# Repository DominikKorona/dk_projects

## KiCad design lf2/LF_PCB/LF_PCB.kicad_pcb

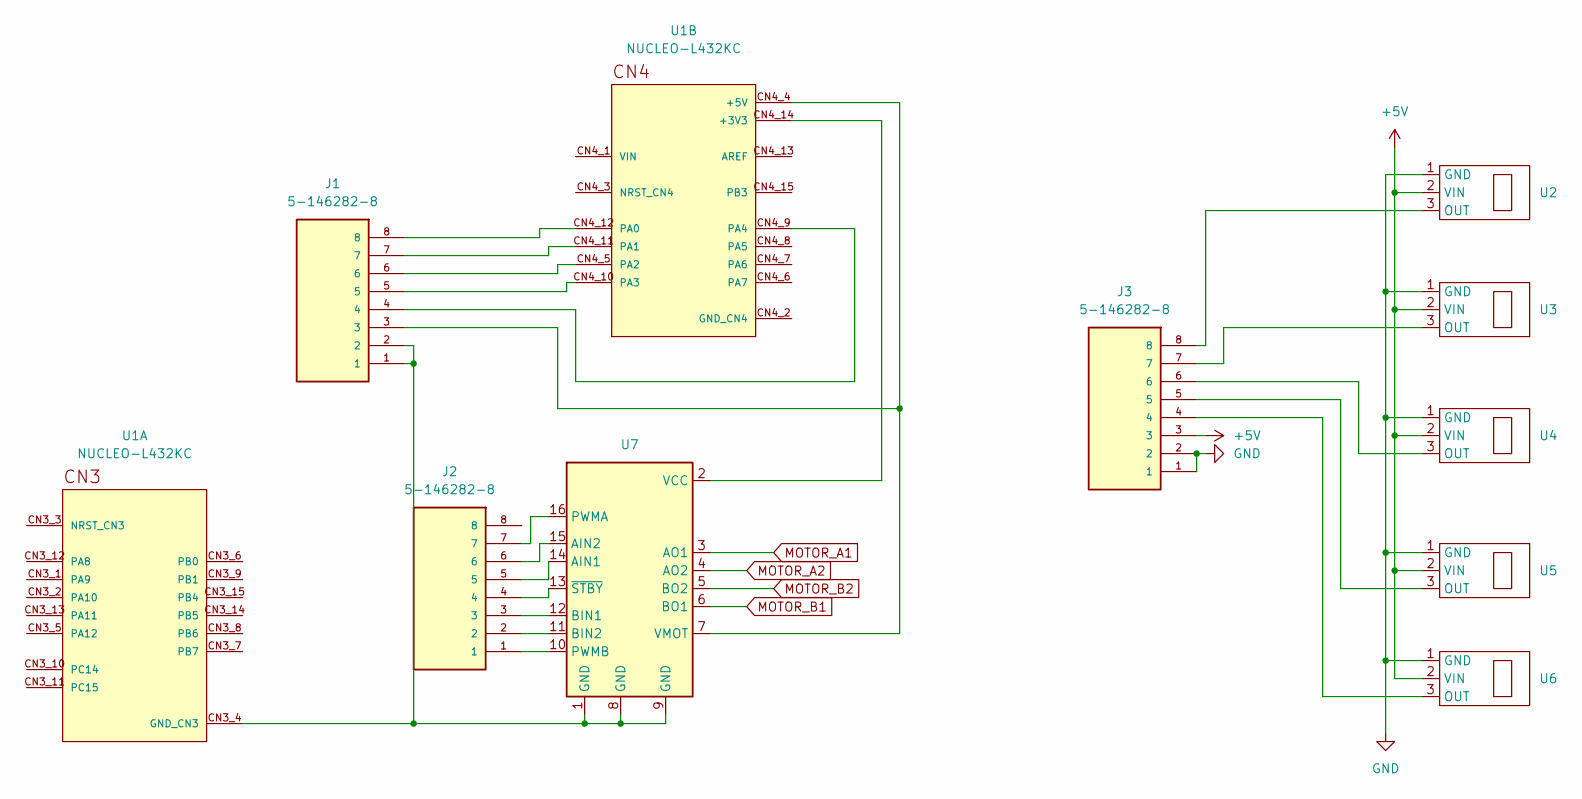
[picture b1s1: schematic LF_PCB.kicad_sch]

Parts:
J1, J2, J3: 5-146282-8; TE_5-146282-8; PARTREV R
U1: NUCLEO-L432KC; MODULE_NUCLEO-L432KC; PARTREV N/A
U2, U3, U4, U5, U6: KTIR_mod
U7: Pololu_Breakout-16_15.2x20.3mm

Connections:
+5V: J3.3, U2.2 (VIN), U3.2 (VIN), U4.2 (VIN), U5.2 (VIN), U6.2 (VIN)
GND: J3.1, J3.2, U2.1 (GND), U3.1 (GND), U4.1 (GND), U5.1 (GND), U6.1 (GND)
MOTOR_A1: U7.3 (AO1)
MOTOR_A2: U7.4 (AO2)
MOTOR_B1: U7.6 (BO1)
MOTOR_B2: U7.5 (BO2)
unnamed: J1.1, J1.2, U1.CN3_4 (GND_CN3), U7.1 (GND), U7.8 (GND), U7.9 (GND)
unnamed: U1.CN4_14 (+3V3), U7.2 (VCC)
unnamed: J1.3, U1.CN4_4 (+5V), U7.7 (VMOT)
unnamed: J1.8, U1.CN4_12 (PA0)
unnamed: J1.7, U1.CN4_11 (PA1)
unnamed: J1.6, U1.CN4_5 (PA2)
unnamed: J1.5, U1.CN4_10 (PA3)
unnamed: J1.4, U1.CN4_9 (PA4)
unnamed: J3.8, U2.3 (OUT)
unnamed: J3.7, U3.3 (OUT)
unnamed: J3.6, U4.3 (OUT)
unnamed: J3.5, U5.3 (OUT)
unnamed: J3.4, U6.3 (OUT)
unnamed: J2.5, U7.14 (AIN1)
unnamed: J2.6, U7.15 (AIN2)
unnamed: J2.3, U7.12 (BIN1)
unnamed: J2.2, U7.11 (BIN2)
unnamed: J2.7, U7.16 (PWMA)
unnamed: J2.1, U7.10 (PWMB)
unnamed: J2.4, U7.13 (~STBY)

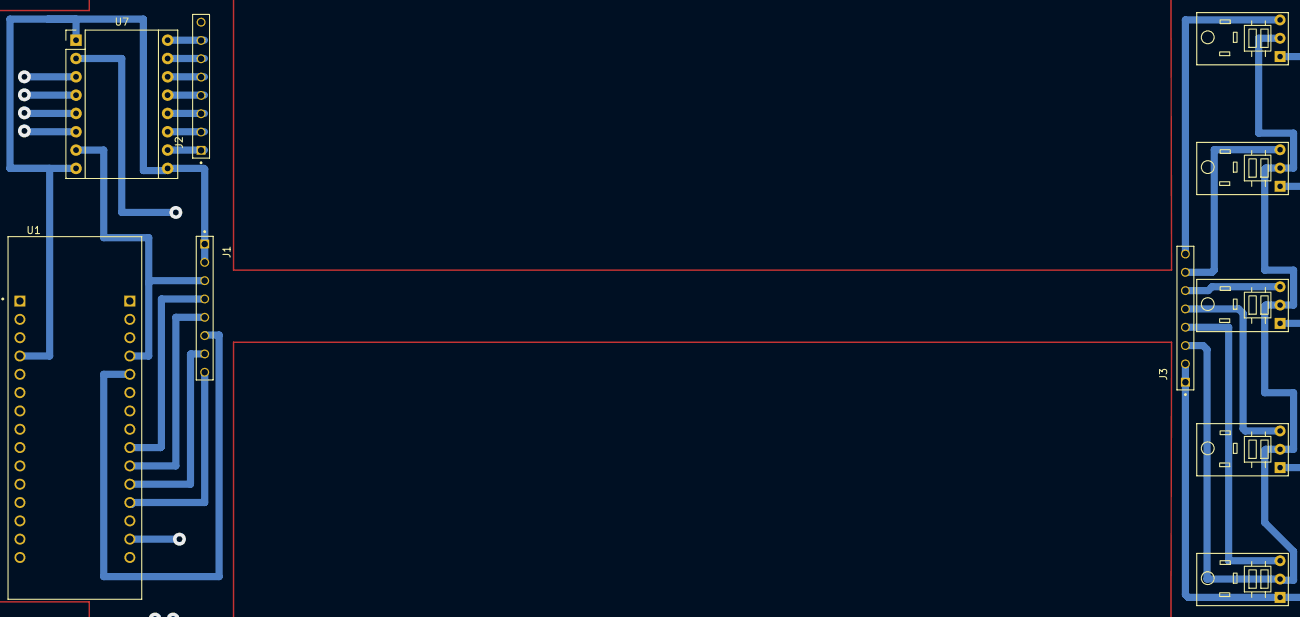
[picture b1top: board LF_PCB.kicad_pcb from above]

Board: 2 copper layers, 10 parts (0 on the bottom side), 22 nets.

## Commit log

2023-05-12 cies
2023-05-29 sprawko5
2023-07-04 diploma
2023-08-03 cpp added
2023-08-03 python
    dodany stary projekt
2023-08-03 deleted
2023-08-03 wykrywka
2023-08-03 metal
2023-08-03 mirror
2023-09-30 lf beginning
2023-10-13 uarty adcki
2023-10-21 push gripper
2023-10-25 add OLED file
    stricte connected with diploma
2023-10-28 add universal
2023-10-28 rozdzielone na dwa pliki
2023-10-28 push pointers
2023-10-28 dzialajace
2023-10-28 3 warstwy abstrakcji added
    >funkcje
    >inicjalizacja
    >gram
2023-11-02 standard display
2023-11-06 format 16bit has changed to 8bit
    Changed data format from 16-bit to 8-bit for improved efficiency and reduced memory usage
2023-11-10 two displays initialized
2023-11-24 I2C, SPI, I2C DMA works, but not spi dma
2024-01-06 diploma thesis
    last update
2024-01-06 last update
2024-01-06 diploma thesis
    replace names ssd1306_ to oled_
2024-02-17 deleted items
2024-03-01 dodanie chowania sie
2024-03-02 dodane bazowanie
2024-03-02 dodano opisy
2024-03-05 dodane czlapanie
2024-03-05 komentarze dodane
2024-07-21 add readme
2024-12-08 Dodano folder ZZUM_laboratorium
2024-12-08 testowy branch
2024-12-08 sprawdzona kamerka i sterowanie silnikami
2024-12-09 sprawdzona kamera i lekkoi skalibrowana
2024-12-09 still poprawiane
2024-12-09 dodane kilka rzeczy
2024-12-10 poprawione czujniki z regulatorami
2024-12-10 dodana kamerka i miejsce na regulator
2024-12-16 dodana kamera z pidem
2024-12-16 zmiany na zajeciach
2025-01-27 najnowwszy kod
2025-02-07 3d objects
